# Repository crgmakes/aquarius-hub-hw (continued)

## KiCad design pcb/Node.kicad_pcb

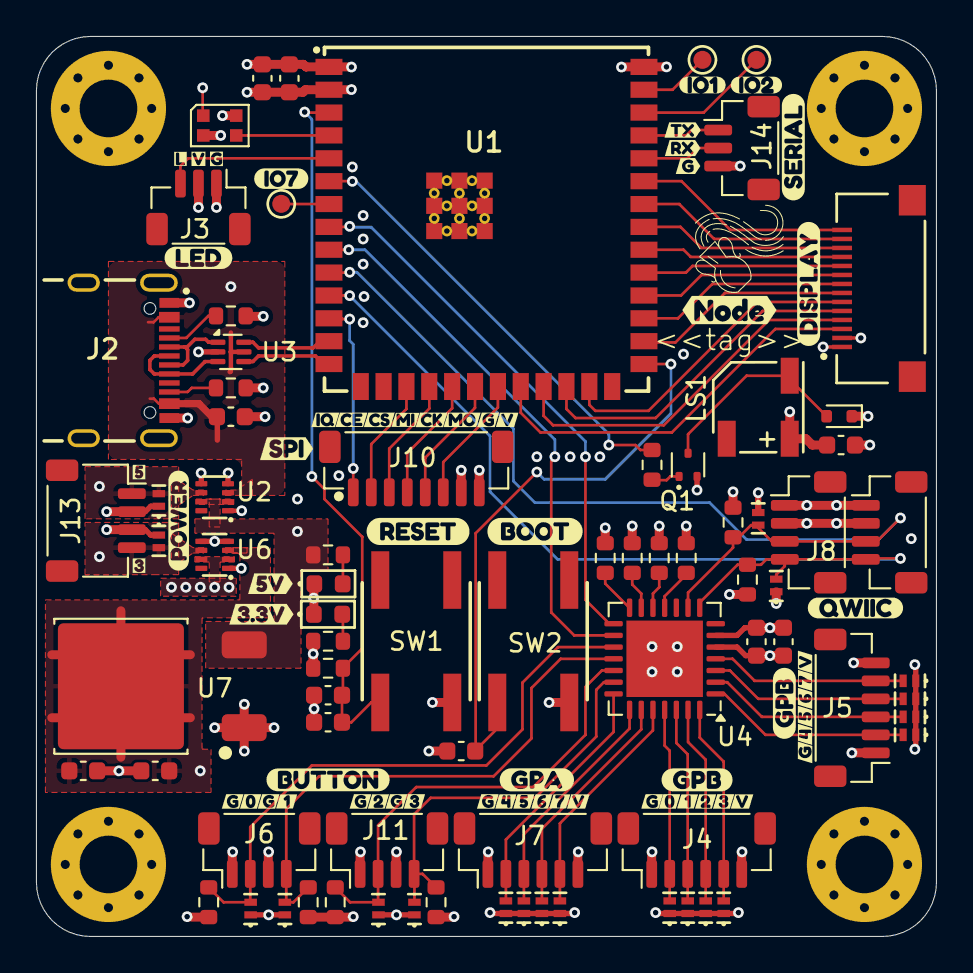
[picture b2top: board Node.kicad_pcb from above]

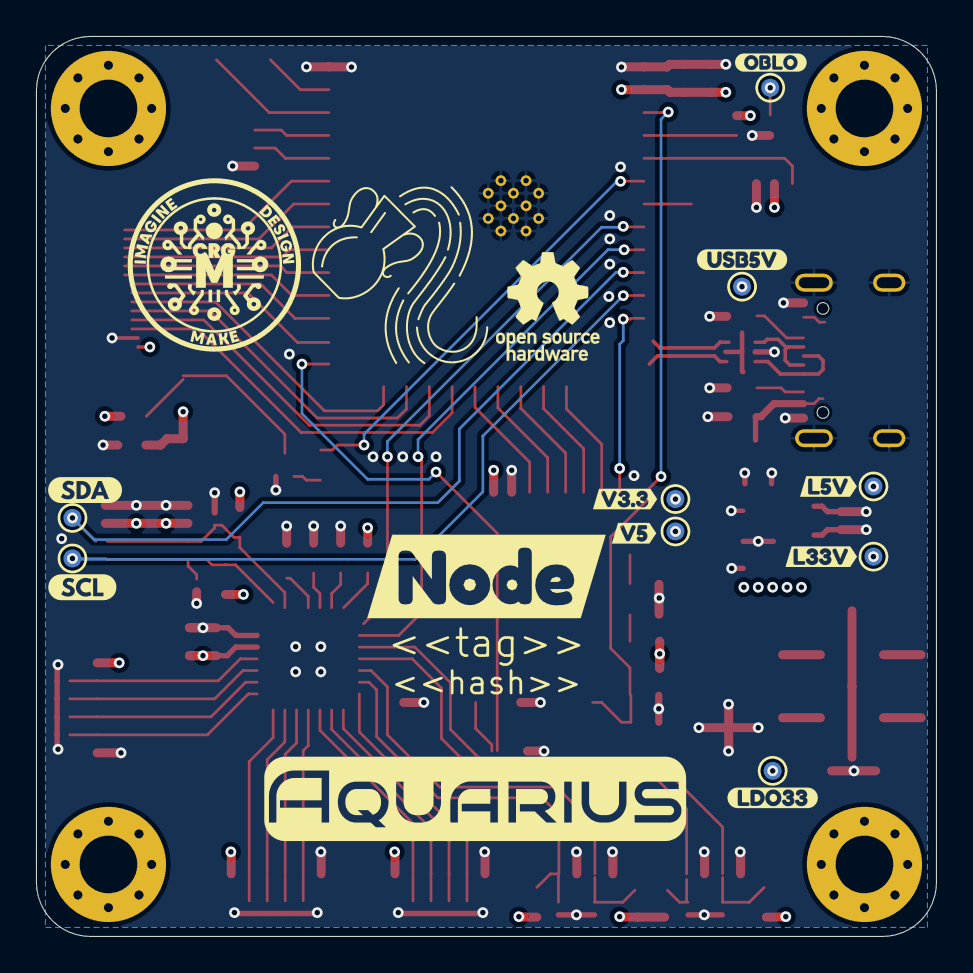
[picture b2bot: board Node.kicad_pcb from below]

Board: 4 copper layers, 50.0 x 50.0 mm, 164 parts (22 on the bottom side), 70 nets.

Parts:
C1, C4, C5, C6, C9: 0.1uF; C_0603_1608Metric
C2, C11, C12: 10uF; C_0603_1608Metric
C3, C10, C14: 1uF; C_0603_1608Metric
D1: WS2812B-2020; LED_WS2812B-2020_PLCC4_2.0x2.0mm
D2: D_Schottky; D_SOD-523
D4, D5, D6, D7, D8, D9, D10, D11, D12, D13, D14, D15, D16, D17, D18, D19, D21, D22, D25: PESD3V3S1BL; DFN1006-2
D20: PESD5V5C1BL; DFN1006-2
D23: Orange; LED_0603_1608Metric
D24: Blue; LED_0603_1608Metric
H1, H2, H3, H4: MountingHole_Pad; MountingHole_3.2mm_M3_Pad_Via
J1: XF2M-1415-1A
J2: USB_C_USB2.0_16P; GCT_USB4105-GF-A
J3, J14: BM03B-SRSS-TB; JST_SH_BM03B-SRSS-TB_1x03-1MP_P1.00mm_Vertical
J4, J5, J7: BM06B-SRSS-TB; JST_SH_BM06B-SRSS-TB_1x06-1MP_P1.00mm_Vertical
J6, J8, J9, J11: BM04B-SRSS-TB; JST_SH_BM04B-SRSS-TB_1x04-1MP_P1.00mm_Vertical
J10: BM08B-SRSS-TB; JST_SH_BM08B-SRSS-TB_1x08-1MP_P1.00mm_Vertical
J13: SM04B-SRSS-TB; JST_SH_SM04B-SRSS-TB_1x04-1MP_P1.00mm_Horizontal
LOGO1: CRGM Logo 5mm
LOGO2: Aquarius Logo 10mm
LOGO3: OSHW-Logo_5.7x6mm_SilkScreen
LOGO4: Aquarius Logo 5mm
LS1: FUET-5025
Q1: MMBT2222A; SOT-523
R1, R2, R15: 4.7K; R_0603_1608Metric
R3, R4, R5, R6, R7, R8, R9, R13, R14: 10K; R_0603_1608Metric
R10, R11: 5.1K; R_0603_1608Metric
R12, R16: 1K; R_0603_1608Metric
SW1, SW2: EVQ-Q2B02W
TP1, TP2, TP3, TP4, TP5, TP6, TP7, TP8, TP9, TP10, TP11, TP12: TP; TestPoint_Pad_D1.0mm
U1: ESP32-S3-WROOM-1-N8R2
U2, U6: LM66200DRLR; SOTFL50P160X60-8N
U3: USBLC6-2P6; SOT-666
U4: MCP23017T-E/ML; QFN-28-1EP_6x6mm_P0.65mm_EP4.25x4.25mm
U7: AZ1084-3.3; TO-252-2
kibuzzard-67B9F9C2: G***; kibuzzard-67B9F9C2
kibuzzard-67B9F9CD: G***; kibuzzard-67B9F9CD
kibuzzard-680D06A5: G***; kibuzzard-680D06A5
kibuzzard-680D069E: G***; kibuzzard-680D069E
kibuzzard-680D0262: G***; kibuzzard-680D0262
kibuzzard-683B54B0: G***; kibuzzard-683B54B0
kibuzzard-683B594D: G***; kibuzzard-683B594D
kibuzzard-683B5370: G***; kibuzzard-683B5370
kibuzzard-683B5376: G***; kibuzzard-683B5376
kibuzzard-683C500B: G***; kibuzzard-683C500B
kibuzzard-683C5017: G***; kibuzzard-683C5017
kibuzzard-685EFB19: G***; kibuzzard-685EFB19
kibuzzard-6812E3A0: G***; kibuzzard-6812E3A0
kibuzzard-6812E3AD: G***; kibuzzard-6812E3AD
kibuzzard-6812E3BB: G***; kibuzzard-6812E3BB
kibuzzard-6812E3C5: G***; kibuzzard-6812E3C5
kibuzzard-6812E37E: G***; kibuzzard-6812E37E
kibuzzard-6812E420: G***; kibuzzard-6812E420
kibuzzard-68153CC4, kibuzzard-68153CC4#2, kibuzzard-68153CC4#3: G***; kibuzzard-68153CC4
kibuzzard-68153CC9: G***; kibuzzard-68153CC9
kibuzzard-68153CCE: G***; kibuzzard-68153CCE
kibuzzard-68153CDD: G***; kibuzzard-68153CDD
kibuzzard-68153CE4: G***; kibuzzard-68153CE4
kibuzzard-68153CEB: G***; kibuzzard-68153CEB
kibuzzard-68153CEF: G***; kibuzzard-68153CEF
kibuzzard-68194F3F: G***; kibuzzard-68194F3F
kibuzzard-68194F50: G***; kibuzzard-68194F50
kibuzzard-68366CAF: G***; kibuzzard-68366CAF
kibuzzard-68574A7C: G***; kibuzzard-68574A7C
kibuzzard-68574A8F: G***; kibuzzard-68574A8F
kibuzzard-68574A9F: G***; kibuzzard-68574A9F
kibuzzard-68574AC2: G***; kibuzzard-68574AC2
kibuzzard-68574AD3: G***; kibuzzard-68574AD3
kibuzzard-68574B95: G***; kibuzzard-68574B95
kibuzzard-68574D7F: G***; kibuzzard-68574D7F
kibuzzard-68574D8A: G***; kibuzzard-68574D8A
kibuzzard-68574D75: G***; kibuzzard-68574D75
kibuzzard-68574D94: G***; kibuzzard-68574D94
kibuzzard-681420CD: G***; kibuzzard-681420CD
kibuzzard-681420D1: G***; kibuzzard-681420D1
kibuzzard-681420D5: G***; kibuzzard-681420D5
kibuzzard-681420DA, kibuzzard-681420DA#2: G***; kibuzzard-681420DA
kibuzzard-681420E9: G***; kibuzzard-681420E9
kibuzzard-681420F3: G***; kibuzzard-681420F3
kibuzzard-681421A1: G***; kibuzzard-681421A1
kibuzzard-681421A9: G***; kibuzzard-681421A9
kibuzzard-683921F2: G***; kibuzzard-683921F2
kibuzzard-6810346D: G***; kibuzzard-6810346D
kibuzzard-6810349E: G***; kibuzzard-6810349E
kibuzzard-6814204F, kibuzzard-6814204F#2: G***; kibuzzard-6814204F
kibuzzard-6814212B: G***; kibuzzard-6814212B
kibuzzard-6815408B: G***; kibuzzard-6815408B
kibuzzard-6857318D: G***; kibuzzard-6857318D
kibuzzard-68103881: G***; kibuzzard-68103881
kibuzzard-68142030, kibuzzard-68142030#2: G***; kibuzzard-68142030
kibuzzard-68142039, kibuzzard-68142039#2: G***; kibuzzard-68142039
kibuzzard-68142043, kibuzzard-68142043#2: G***; kibuzzard-68142043
kibuzzard-68142110: G***; kibuzzard-68142110
kibuzzard-68142199: G***; kibuzzard-68142199
kibuzzard-68154095, kibuzzard-68154095#2, kibuzzard-68154095#3: G***; kibuzzard-68154095
kibuzzard-68392226: G***; kibuzzard-68392226

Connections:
+3.3V: C1.1, C2.1, C9.1, C10.1, C14.1, D1.4 (VDD), D2.1 (K), J1.1, J3.2, J4.6, J5.6, J7.6, J8.2, J9.2, J10.8, LS1.2 (+), R1.1, R2.1, R3.1, R4.1, R5.1, R9.1, R13.1, R14.1, R16.1, TP8.1, U1.2 (3V3), U4.5 (VDD), U6.2 (VOUT1), U6.7 (VOUT2)
+5V: R15.1, TP12.1, U2.2 (VOUT1), U2.7 (VOUT2), U7.3 (VI)
/PIO/A0: R6.1, U4.11 (A0)
/PIO/A1: R7.1, U4.12 (A1)
/PIO/A2: R8.1, U4.13 (A2)
/PIO/BTN0: D12.2 (K2), J6.2, R14.2, U4.17 (GPA0)
/PIO/BTN1: D13.2 (K2), J6.4, R13.2, U4.18 (GPA1)
/PIO/BTN2: D14.2 (K2), J11.2, R5.2, U4.19 (GPA2)
/PIO/BTN3: D15.2 (K2), J11.4, R4.2, U4.20 (GPA3)
/PIO/GPA4: D16.2 (K2), J7.2, U4.21 (GPA4)
/PIO/GPA5: D17.2 (K2), J7.3, U4.22 (GPA5)
/PIO/GPA6: D18.2 (K2), J7.4, U4.23 (GPA6)
/PIO/GPA7: D19.2 (K2), J7.5, U4.24 (GPA7)
/PIO/GPB0: D4.2 (K2), J4.2, U4.25 (GPB0)
/PIO/GPB1: D5.2 (K2), J4.3, U4.26 (GPB1)
/PIO/GPB2: D6.2 (K2), J4.4, U4.27 (GPB2)
/PIO/GPB3: D7.2 (K2), J4.5, U4.28 (GPB3)
/PIO/GPB4: D8.2 (K2), J5.2, U4.1 (GPB4)
/PIO/GPB5: D9.2 (K2), J5.3, U4.2 (GPB5)
/PIO/GPB6: D10.2 (K2), J5.4, U4.3 (GPB6)
/PIO/GPB7: D11.2 (K2), J5.5, U4.4 (GPB7)
/PIO/PIO_RESET: R9.2, U4.14 (~RESET)
/Peripherals/BUZZ_GND: D2.2 (A), LS1.3 (-), Q1.3 (C)
/Power/CC1: J2.A5 (CC1), R11.1
/Power/CC2: J2.B5 (CC2), R10.1
/Power/V3.3LED: D24.2 (A), R16.2
/Power/V5LED: D23.2 (A), R15.2
BOOT: C5.1, SW2.B1 (B), U1.27 (IO0)
BUZZER: R12.1, U1.6 (IO6)
D_N: U1.13 (USB_D-), U3.6 (I/O1)
D_P: U1.14 (USB_D+), U3.4 (I/O2)
EN: C3.1, C4.1, R3.2, SW1.B1 (B), U1.3 (EN)
GND: C1.2, C2.2, C3.2, C4.2, C5.2, C6.2, C9.2, C10.2, C11.2, C12.2, C14.2, D1.2 (VSS), D4.1 (K1), D5.1 (K1), D6.1 (K1), D7.1 (K1), D8.1 (K1), D9.1 (K1), D10.1 (K1), D11.1 (K1), D12.1 (K1), D13.1 (K1), D14.1 (K1), D15.1 (K1), D16.1 (K1), D17.1 (K1), D18.1 (K1), D19.1 (K1), D20.1 (K1), D21.1 (K1), D22.1 (K1), D23.1 (K), D24.1 (K), D25.1 (K1), J1.2, J2.A1B12 (GND), J2.B1A12 (GND), J2.S1 (SHIELD), J3.1, J4.1, J5.1, J6.1, J6.3, J7.1, J8.1, J9.1, J10.7, J11.1, J11.3, J13.2 (GND), J13.3 (GND), J14.3, Q1.2 (E), R6.2, R7.2, R8.2, R10.2, R11.2, SW1.A1 (A), SW2.A1 (A), U1.1 (GND), U1.40 (GND), U1.41 (GND), U2.1 (GND1), U2.4 (~ON), U2.5 (GND2), U3.2 (GND), U4.6 (VSS), U4.29 (EP), U6.1 (GND1), U6.4 (~ON), U6.5 (GND2), U7.1 (GND)
I2C_SCL: D21.2 (K2), J8.4, J9.4, R2.2, TP2.1, U1.11 (IO18), U4.8 (SCK)
I2C_SDA: D22.2 (K2), J8.3, J9.3, R1.2, TP1.1, U1.10 (IO17), U4.9 (SDA)
LCD_BL: J1.8, U1.29 (IO36)
LCD_CS: J1.3, U1.22 (IO14)
LCD_DC: J1.5, U1.24 (IO47)
LCD_RS: J1.4, U1.23 (IO21)
LCD_SCK: J1.7, U1.28 (IO35)
LCD_SDI: J1.6, U1.25 (IO48)
LCD_SDO: J1.9, U1.30 (IO37)
LDO_V33: C11.1, C12.1, TP9.1, U6.3 (VIN1), U7.2 (VO)
LEDS: J3.3, U1.5 (IO5)
LINE_5V: D20.2 (K2), J13.1 (V5), TP10.1, U2.6 (VIN2)
LINE_V33: D25.2 (K2), J13.4 (V3.3), TP11.1, U6.6 (VIN2)
unnamed: Q1.1 (B), R12.2
unnamed: TP5.1, U1.39 (IO1)
unnamed: TP6.1, U1.38 (IO2)
unnamed: TP7.1, U1.7 (IO7)
OBL: D1.3 (DIN), U1.4 (IO4)
OBL_OUT: D1.1 (DOUT), TP3.1
PIO_INTA: U1.8 (IO15), U4.15 (INTB)
PIO_INTB: U1.9 (IO16), U4.16 (INTA)
RX: J14.2, U1.36 (RXD0)
SD_CS: J1.14, U1.35 (IO42)
SPI_CE0: J10.2, U1.17 (IO9)
SPI_CLK: J10.5, U1.20 (IO12)
SPI_CS0: J10.3, U1.18 (IO10)
SPI_IRQ0: J10.1, U1.12 (IO8)
SPI_MISO: J10.4, U1.19 (IO11)
SPI_MOSI: J10.6, U1.21 (IO13)
TX: J14.1, U1.37 (TXD0)
T_INT: J1.13, U1.34 (IO41)
T_RESET: J1.11, U1.32 (IO39)
T_SCL: J1.10, U1.31 (IO38)
T_SDA: J1.12, U1.33 (IO40)
USB_5V: C6.1, J2.A4B9 (VBUS), J2.B4A9 (VBUS), TP4.1, U2.3 (VIN1), U3.5 (VBUS)
USB_D_N: J2.A7 (D-), J2.B7 (D-), U3.1 (I/O1)
USB_D_P: J2.A6 (D+), J2.B6 (D+), U3.3 (I/O2)

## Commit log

2025-03-22 Initial license file
2025-04-29 Major updates to IO and board size
    some issue with display of properties in schematic view.
2025-04-30 Added buzzer
2025-05-01 Changed SPI to 8 pin connector
2025-05-02 Added additional labels; minor clean up.
2025-05-05 added open hw; changed test points; added pulls on buttons
    change buttons to be 2 connectors with pull ups.
2025-05-05 added 1x2 panel
2025-05-08 Change panel to be 1x1
    Changed connectors be vertical rather than horizontal.
    Updated TVS diodes to DFN1006 rather than SMF
2025-06-01 Major overhaul of IO
    Added GPIO module
    Added SPI interface
    Added serial interface
    Added power selection
    Added power LEDs
    Changed v3.3 LDO
2025-06-01 Updated raytracing images on main page
2025-06-01 Added release workflow
2025-06-02 Fixed MPN mismatches and other fields
2025-06-02 Filleted PCB corners
2025-06-02 Switched from mouse bites to v score
2025-06-03 Removed duplicative ESB on USB
    Updated descriptions for consistency
2025-06-07 Fixed cap values on reset button
    Fixed all part numbers and extended parameters.
2025-06-09 Rationalized attributes; excluded some footprints from BOM
2025-06-21 Continued rationalizing parts
2025-06-21 Updated dimensions; updated mounting hole footprint
2025-06-21 Adjusted part values
    Fixed LCSC footprints for connectors
    Moved EN 5% instead of 1%
    Moved I2C pull ups to 4.7K
2025-06-22 Cleaned up fab layer. Minor tweaks. Updated renders.
2025-06-23 closed #3 and #1
    Fixed resistors and values
    Widened panel
2025-06-24 removed v-cut offset; moved v-cut to edge.cuts layer
2025-06-24 updated ci script to include date of release and cash in schematic
2025-06-24 added checkin hash to title block
2025-06-24 added all schematics to tagging; remove unused files
2025-06-24 removed duplicative sed lines
2025-06-26 Updated frame template
2025-06-26 Added PCB requirements to requirements sheet; adjusted user drawing layer a little
2025-06-26 Fixed serial model; fixed CI script
2025-06-27 Updated worksheet template
2025-06-27 Updated worksheet template and logo
2025-06-27 fixed case of release file name.
2025-06-28 Fixed footprint for Buzzer, XFC, USB ESD, and Power Switcher
2025-06-28 Moved termal vias.
2025-06-28 Updated PCB for DFM
2025-06-28 Fixed missing packages
2025-06-28 Fixed module path for buzzer
2025-06-29 Minor trace clean up; set stack up colors.
2025-06-29 Added full frame for JLC
2025-07-13 Added test points. Fixed license file.
2025-07-24 Updated license and minor schematic changes
2025-08-11 Minor updates to ESP part number/footprint
2025-08-12 Changed Node to Hub
2025-08-12 Changed name to hub
2025-08-12 Change name in schematic
2025-08-14 changed git runner to use central file
2025-08-14 Changed graphics to Hub from Node
2025-08-23 Renamed files; update with more test points
2025-08-23 Renamed peripherals to interfaces; added test points; added led jumper
2025-08-28 Updated panel properties
2025-08-31 Adjusting for consistency
2025-09-02 Sync symbols and footprints
    Transitioned to CRGM footprints
    Added dimensions
    Fixed some spacing
    Adjusted properties
2025-09-06 Clean up and consistency
    Moved buzzer to MCU
    Fixed model directory
    Set font size
    Set outline size
    Upscaled Roxy ❤️
2025-09-06 Fixed git action pointer
2025-09-08 Updated part attributes for consistency.
    Updated requirements section to be more accurate.
2025-09-09 fixed LCSC part numbers
2025-10-23 Switched to internal and external I2C bus
    Updated renders
    Updated description of QWICC connectors
    Added test points for INT I2C
2025-10-26 Updated .gitignore
2025-10-27 Rework to add power connector
    Simplified GPIO connectors to make sure for power.
2025-10-28 Moved connectors
    Moved I2C to edge
    Rearranged all GPIO
    Re-routed as necessary
    (I don't like the button connector layout -- like the old way more)
2025-10-29 Fixed GPIO resistor annoyance
    Better ground now
    Stitching vias all around
2025-11-02 Updated silkscreen
2025-11-02 Aligned labels.
2025-11-04 renamed pio to peripheral
2025-11-16 Added board stack up to user comment layer
2025-11-25 Added bulk caps to v3.3 for better smoothing
2025-12-18 Moved to vertical connectors
2025-12-19 Changed button connector to ground every other
2025-12-22 Added 220uF cap on Power
    Rearranged accordingly
    Can be upgraded to 470uF if required.
2025-12-27 Updated cooper pour
    Updated footprint for TO-252-3
    Adjusted pours
    Adjusted spacing
    Change buzzer and LED names on schematic
2025-12-29 Fixed power input
    Removed 3.3v selection
    Removed unnecessary caps
    Rerouted as necessary
    Fixed silkscreen
2025-12-29 Updated renders
    Minor clean up.
2026-02-18 Upgraded to N16R2
2026-02-24 Minor silkscreen changes.
    Updated 2222 footprint
    Ready for next release
2026-02-25 Temoved duplicative test points
    Cleaned up routing and silkscreen.
    Updated mounting holes and tied to ground.
2026-02-27 Added TVS to LED and Serial
    Minor silkscreen updates
2026-03-01 replaced .wrl with .step
2026-03-06 Fixed part placement and missing model
    Both display and 3.3 regulator were in the wrong place after updating from library!
    LED was missing model
    Minor silkscreen changes
    Updated renders
2026-03-06 Fixed silkscreen on pad issue
2026-03-06 Updated models and values
    Updated ESP value to N16R2
    Cleaned up test points for LCD
    Changed to N16R2 model
2026-03-06 Fixed value property for MCU
    removed filters from ESP32 symbol
2026-03-12 Updated foot prints and symbols
2026-03-12 Updated footprints and rotations
2026-03-12 Fixed LCSC part # for power connector
2026-03-13 Fixed part numbers
    Fixed 3 pin JST LCSC Part Number
    Fixed MPN for JST 3 pin
    Changed Hub to Node on top silkscreen
    Updated renders
2026-05-28 Added analog port
    re-routed
    resized the pretty princess
